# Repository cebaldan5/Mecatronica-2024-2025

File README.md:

# Mecatronica-2024-2025
Repositorio para la clase mecatrónica (2327003) URJC

Esto va en otra línea

## Otro apatrado

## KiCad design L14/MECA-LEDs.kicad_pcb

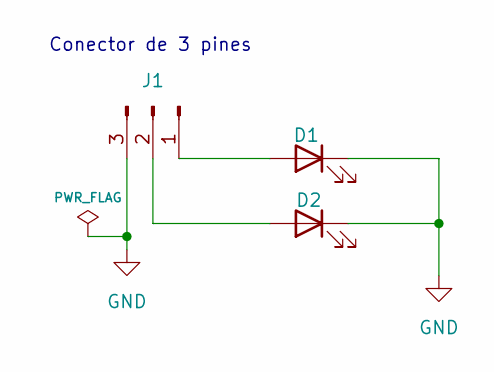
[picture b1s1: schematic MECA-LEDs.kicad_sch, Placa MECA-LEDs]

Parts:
D1, D2: LED; LED_D3.0mm
J1: Conn_01x03_Pin; PinHeader_1x03_P2.54mm_Vertical

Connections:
GND: D1.1 (K), D2.1 (K), J1.3
unnamed: D1.2 (A), J1.1
unnamed: D2.2 (A), J1.2

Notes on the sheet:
Conector de 3 pines

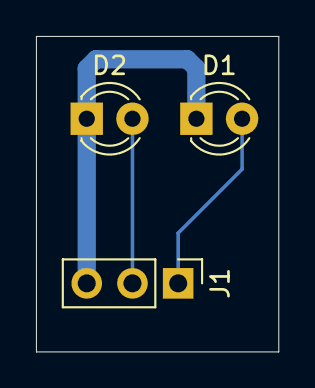
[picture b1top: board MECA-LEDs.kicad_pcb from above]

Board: 2 copper layers, 13.5 x 17.5 mm, 3 parts (0 on the bottom side), 3 nets.

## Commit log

2024-09-11 escuela TEC
2024-09-11 borrar captura
2024-09-11 fotos de logos de programas
2024-09-16 circulo
2024-09-16 cambios L3
2024-09-17 dubujo + test
2024-09-18 hacer y mover L4
2024-09-18 reto 3
2024-09-18 cambio smiley
2024-09-18 añadir
2024-09-21 nombre
2024-09-23 notas/dibujos
2024-09-23 mover y crear L5
2024-09-23 pikachu
2024-10-01 añadir a L6
2024-10-01 cambio nombres
2024-10-02 añadir a L7
2024-10-02 fotos
2024-10-07 subir pieza + croquis
2024-10-07 añadir dibujos
2024-10-07 cambio y borrar
2024-10-07 fotos de planos
2024-10-09 extornsionado
2024-10-09 mesa de ikea
2024-10-09 foto de plano
2024-10-09 modificaci+on animágen de grúa
2024-10-11 piezas de mesa IKEA
2024-10-11 imagen del plano
2024-10-16 pinzas
2024-10-21 ensamle y clase del 21 oct
2024-10-22 cambio de nombre carpeta L10
2024-10-22 subir foto a github, va a ser cambiada por plano eventuealmente
2024-10-24 garra a base de paralelogramo
2024-10-28 kicad
2024-10-28 subir kicads
